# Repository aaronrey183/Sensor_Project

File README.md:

18650 LiPo batteries at 3.7v to 3A 3.8v switching regulator

ATMEGA 3208 based development board

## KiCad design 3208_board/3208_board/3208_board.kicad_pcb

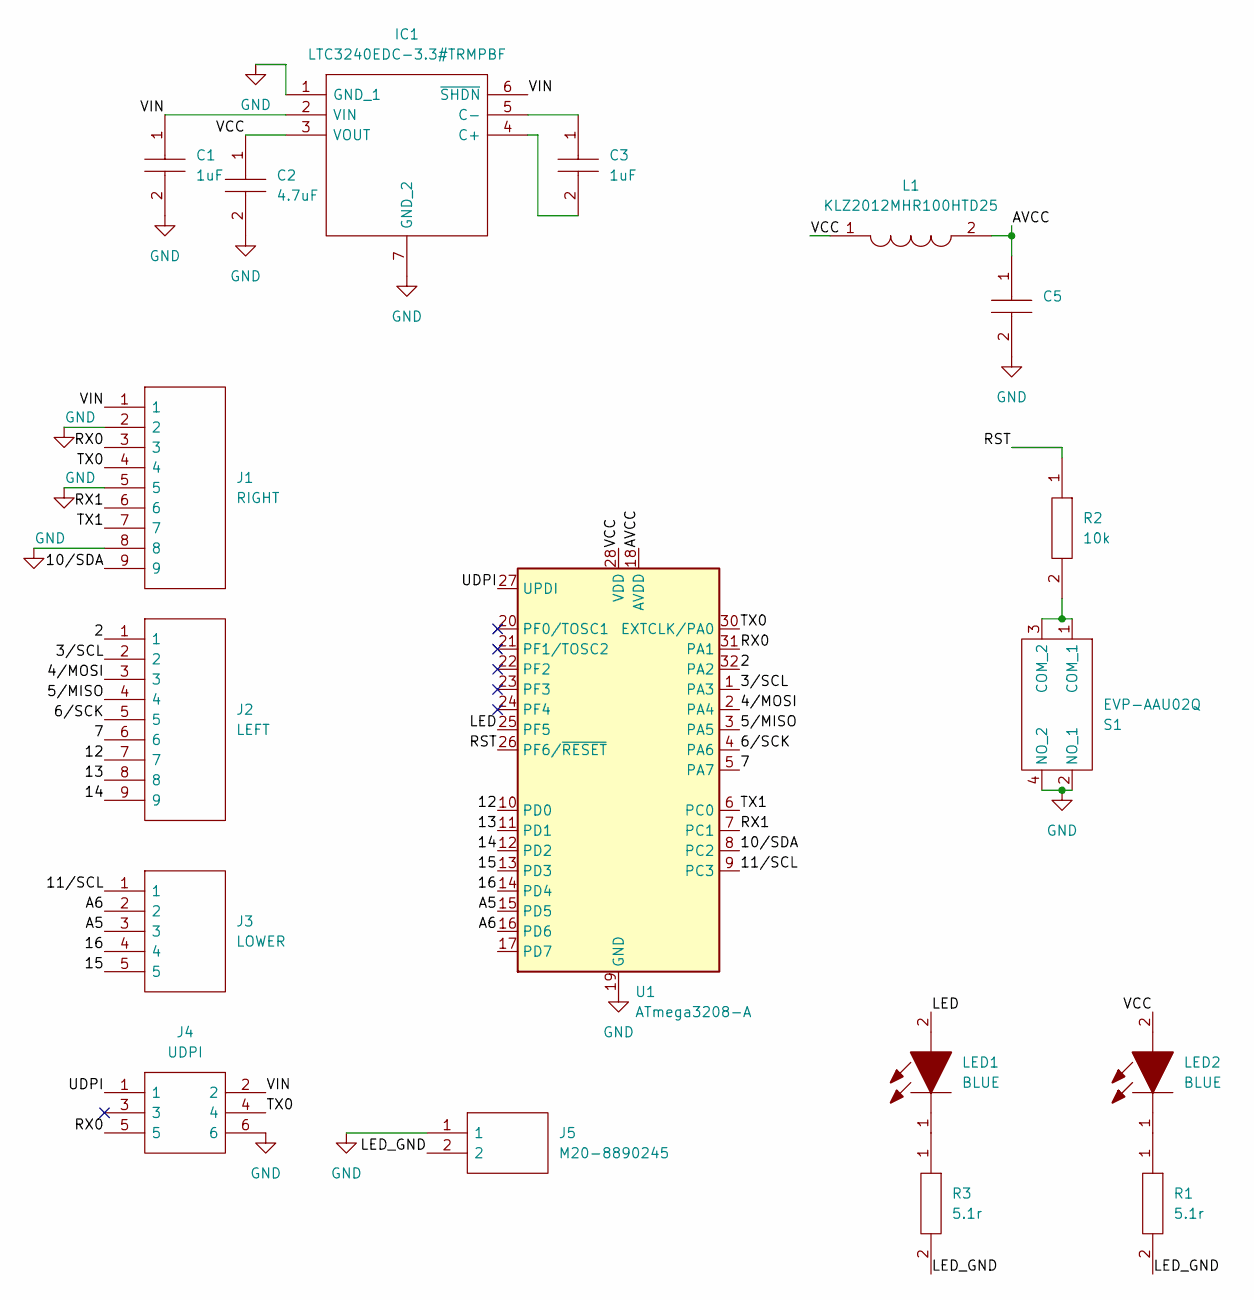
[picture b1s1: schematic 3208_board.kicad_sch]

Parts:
C1, C3: 1uF; CAPC1608X90N; Mouser Part Number 81-GRM188R61C105KA2J
C2: 4.7uF; CAPC1608X90N; Mouser Part Number 81-GRM188R61C105KA2J
C5: GCM188R71C104KA37J; CAPC1608X90N; Mouser Part Number 81-GCM188R71C104KA7J
IC1: LTC3240EDC-3.3#TRMPBF; SON50P200X200X80-7N-D; Mouser Part Number 584-C3240EDC-3.3TMPF
J1: RIGHT; HDRV9W64P0X254_1X9_2286X248X838P; Mouser Part Number 200-HTSW10907LS
J2: LEFT; HDRV9W64P0X254_1X9_2286X248X838P; Mouser Part Number 200-HTSW10907LS
J3: LOWER; HDRV5W64P0X254_1X5_1270X248X838P; Mouser Part Number 200-HTSW10507TMS
J4: UDPI; HDRV6W69P254_2X3_762X498X813P; Mouser Part Number 538-87914-0616
J5: M20-8890245; M208890245; Mouser Part Number 855-M20-8890245
L1: KLZ2012MHR100HTD25; INDC2012X145N; Mouser Part Number 810-KLZ2012MHR100HTD
LED1, LED2: BLUE; LEDC1608X80N; Mouser Part Number 710-150060BS75000
R1, R3: 5.1r; RESC2012X60N; Mouser Part Number 652-CR0805-J/-1R0ELF
R2: 10k; RESC2012X60N; Mouser Part Number 652-CR0805-J/-1R0ELF
S1: EVP-AAU02Q
U1: ATmega3208-A; TQFP-32_7x7mm_P0.8mm

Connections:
/2: J2.1, U1.32 (PA2)
/3/SCL: J2.2, U1.1 (PA3)
/4/MOSI: J2.3, U1.2 (PA4)
/5/MISO: J2.4, U1.3 (PA5)
/6/SCK: J2.5, U1.4 (PA6)
/7: J2.6, U1.5 (PA7)
/10/SDA: J1.9, U1.8 (PC2)
/11/SCL: J3.1, U1.9 (PC3)
/12: J2.7, U1.10 (PD0)
/13: J2.8, U1.11 (PD1)
/14: J2.9, U1.12 (PD2)
/15: J3.5, U1.13 (PD3)
/16: J3.4, U1.14 (PD4)
/A5: J3.3, U1.15 (PD5)
/A6: J3.2, U1.16 (PD6)
/AVCC: C5.1, L1.2, U1.18 (AVDD)
/LED: LED1.2, U1.25 (PF5)
/LED_GND: J5.2, R1.2, R3.2
/RST: R2.1, U1.26 (PF6/~RESET)
/RX0: J1.3, J4.5, U1.31 (PA1)
/RX1: J1.6, U1.7 (PC1)
/TX0: J1.4, J4.4, U1.30 (EXTCLK/PA0)
/TX1: J1.7, U1.6 (PC0)
/UDPI: J4.1, U1.27 (UPDI)
/VCC: C2.1, IC1.3 (VOUT), L1.1, LED2.2, U1.28 (VDD)
/VIN: C1.1, IC1.2 (VIN), IC1.6 (~SHDN), J1.1, J4.2
GND: C1.2, C2.2, C5.2, IC1.1 (GND_1), IC1.7 (GND_2), J1.2, J1.5, J1.8, J4.6, J5.1, S1.2 (NO_1), S1.4 (NO_2), U1.19 (GND), U1.29 (GND)
unnamed: C3.1, IC1.5 (C-)
unnamed: C3.2, IC1.4 (C+)
unnamed: LED1.1, R3.1
unnamed: LED2.1, R1.1
unnamed: R2.2, S1.1 (COM_1), S1.3 (COM_2)

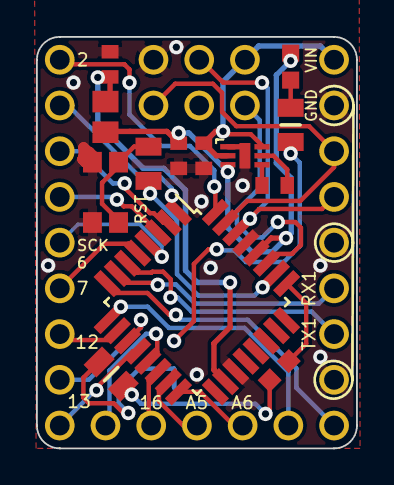
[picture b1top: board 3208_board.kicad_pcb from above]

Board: 2 copper layers, 17.8 x 22.9 mm, 18 parts (1 on the bottom side), 32 nets.

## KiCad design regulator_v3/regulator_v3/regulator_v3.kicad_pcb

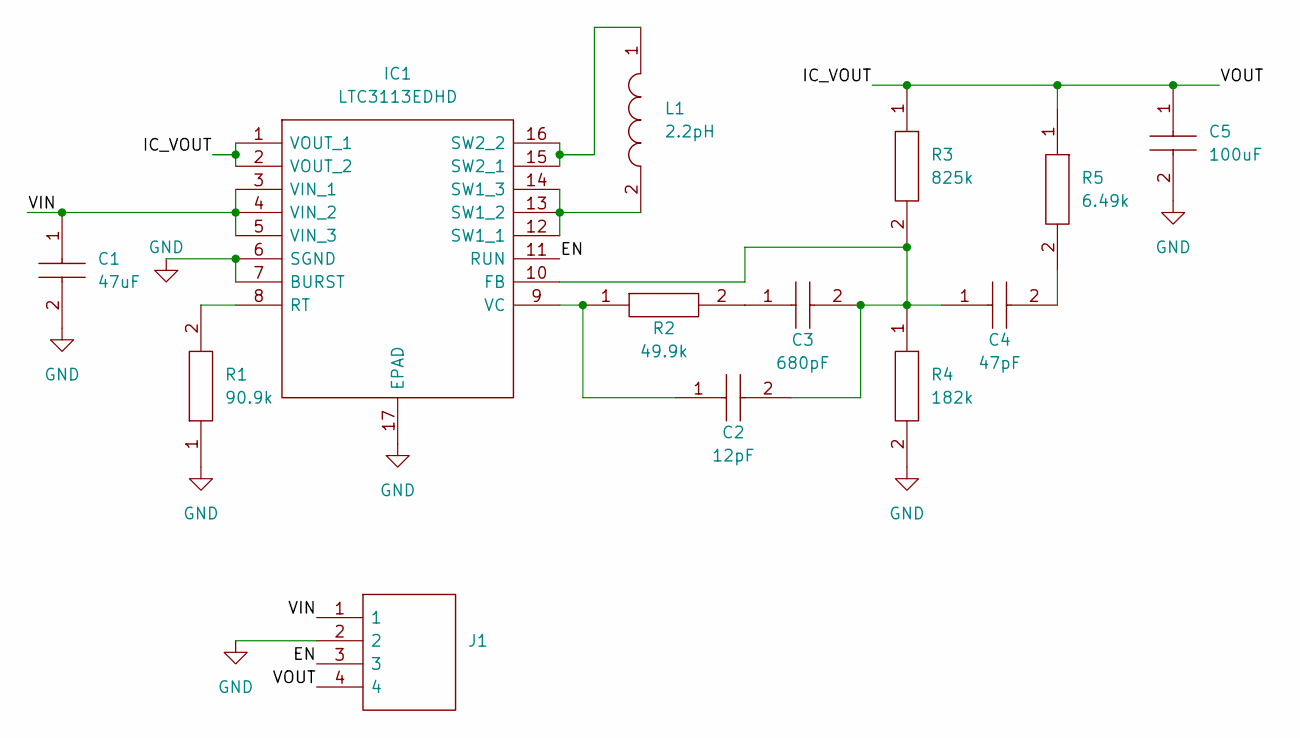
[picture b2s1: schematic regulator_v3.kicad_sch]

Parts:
C1: 47uF; CAPC2012X145N; Mouser Part Number 81-GRM21BR61A476ME5K
C2: 12pF; CAPC1608X90N; Mouser Part Number 81-GCM1885C2A120JA6D
C3: 680pF; CAPC1608X90N; Mouser Part Number 81-GCM1885C2A681J16D
C4: 47pF; CAPC1608X90N; Mouser Part Number 81-GCM1885C2A681J16D
C5: 100uF; CAPC2012X145N; Mouser Part Number 81-GRM21BR61A476ME5K
IC1: LTC3113EDHD; SON50P400X500X80-17N-D; Mouser Part Number 584-LTC3113EDHDTRPBF
J1: M20-9730446; HDRV4W66P0X254_1X4_1016X254X954P; Mouser Part Number 855-M20-9730446
L1: 2.2pH; HCP0704-2R3-R
R1: 90.9k; RESC2012X60N; Mouser Part Number 652-CR0805FX-9092ELF
R2: 49.9k; RESC2012X60N; Mouser Part Number 652-CR0805FX-4992ELF
R3: 825k; RESC2012X60N; Mouser Part Number 652-CR0805FX-1823ELF
R4: 182k; RESC2012X60N; Mouser Part Number 652-CR0805FX-1823ELF
R5: 6.49k; RESC2012X60N; Mouser Part Number 652-CR0805FX-1823ELF

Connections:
/EN: IC1.11 (RUN), J1.3
/IC_VOUT: C5.1, IC1.1 (VOUT_1), IC1.2 (VOUT_2), J1.4, R3.1, R5.1
/VIN: C1.1, IC1.3 (VIN_1), IC1.4 (VIN_2), IC1.5 (VIN_3), J1.1
GND: C1.2, C5.2, IC1.6 (SGND), IC1.7 (BURST), IC1.17 (EPAD), J1.2, R1.1, R4.2
unnamed: C2.1, IC1.9 (VC), R2.1
unnamed: C2.2, C3.2, C4.1, IC1.10 (FB), R3.2, R4.1
unnamed: C3.1, R2.2
unnamed: C4.2, R5.2
unnamed: IC1.8 (RT), R1.2
unnamed: IC1.12 (SW1_1), IC1.13 (SW1_2), IC1.14 (SW1_3), L1.2
unnamed: IC1.15 (SW2_1), IC1.16 (SW2_2), L1.1

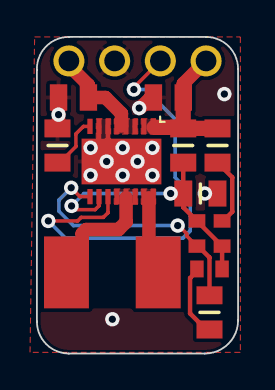
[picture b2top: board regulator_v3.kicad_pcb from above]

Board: 2 copper layers, 11.2 x 17.6 mm, 13 parts (0 on the bottom side), 11 nets.
